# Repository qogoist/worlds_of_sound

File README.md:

# Worlds of Sound

* [Raspberry Pi/Column](/column_tof/pi_setup.md)
* [Arduino/Cube](/arduino_files/arduino_setup.md)

## Dev Tools
* [Max MSP](https://cycling74.com/products/max) is necessary to open the MAX patches which are used as plugins for Ableton.
* [Arduino IDE](https://www.arduino.cc/en/Main/Software) is needed to get the necessary drivers and libraries to write and upload code to the Arduinos.

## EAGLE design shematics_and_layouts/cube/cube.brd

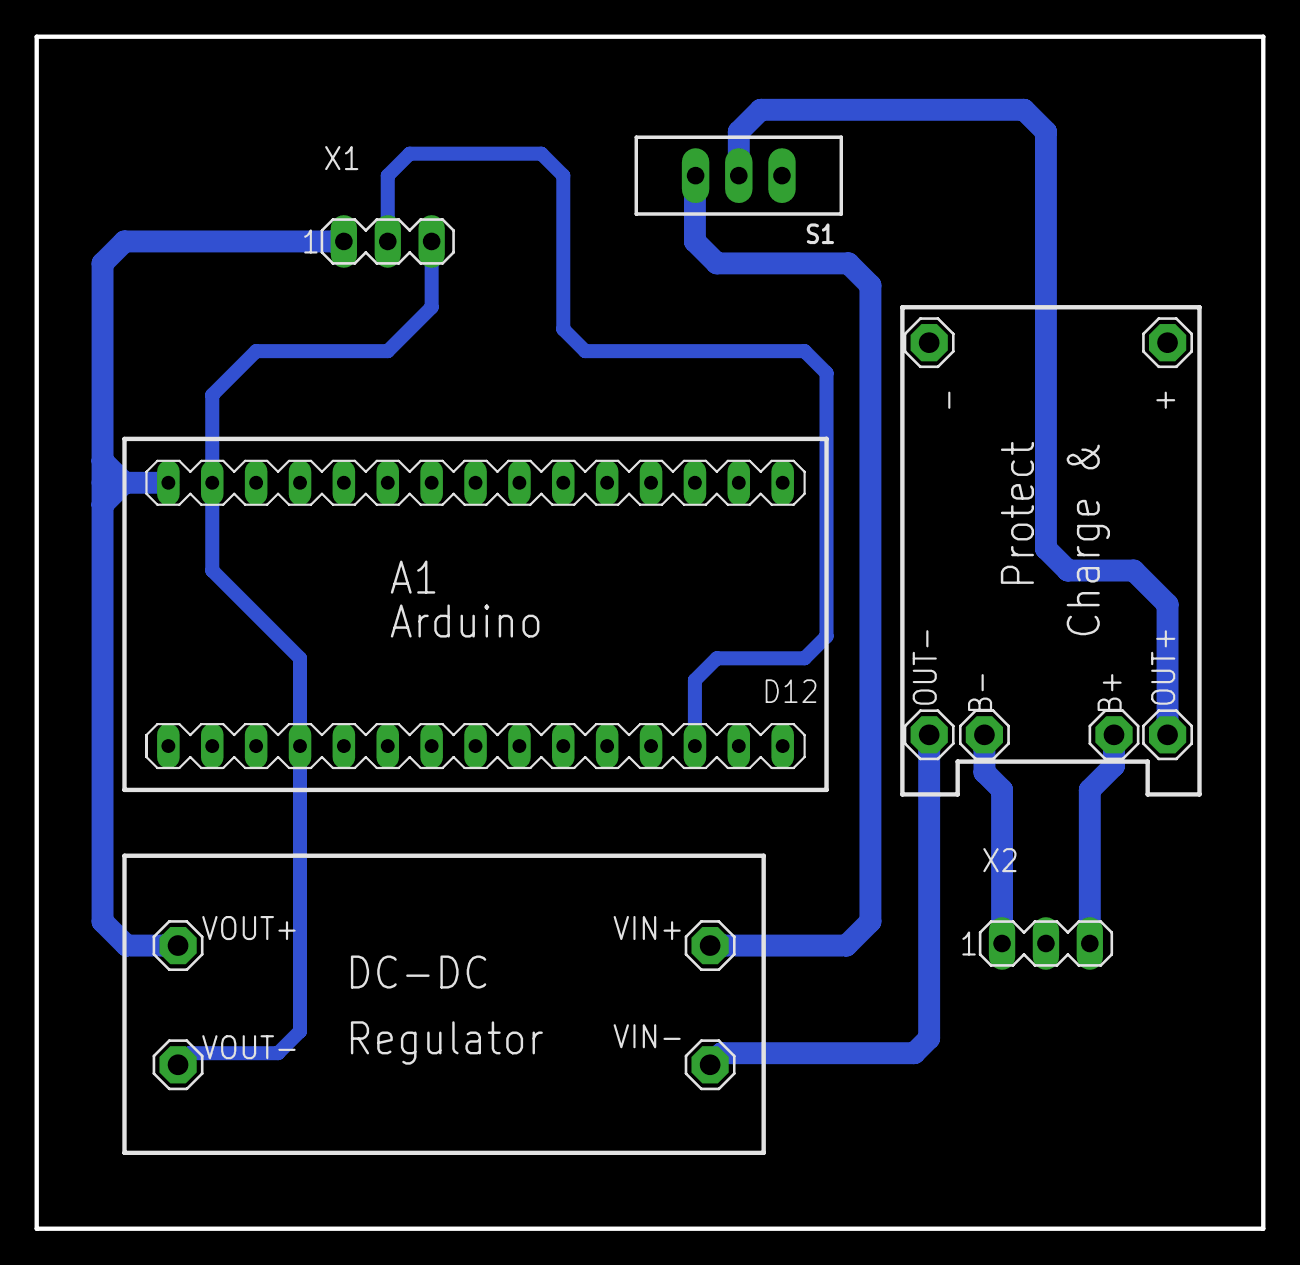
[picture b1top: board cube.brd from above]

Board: 2 copper layers, 71.0 x 69.0 mm, 14 parts (0 on the bottom side), 8 nets.

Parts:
+: MCS08
-: MCS08
A1: NANO
B+: MCS08
B-: MCS08
OUT+: MCS08
OUT-: MCS08
S1: EG1218
VIN+: MCS08
VIN-: MCS08
VOUT+: MCS08
VOUT-: MCS08
X1: LEDs; MA03-1
X2: BAT; MA03-1

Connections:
GND: A1.GND, A1.GND1, VOUT-.MP, X1.3
unnamed: OUT+.MP, S1.2
unnamed: OUT-.MP, VIN-.MP
unnamed: S1.3, VIN+.MP
unnamed: B-.MP, X2.1
unnamed: B+.MP, X2.3
unnamed: A1.D10, X1.2
VCC: A1.RAW, VOUT+.MP, X1.1

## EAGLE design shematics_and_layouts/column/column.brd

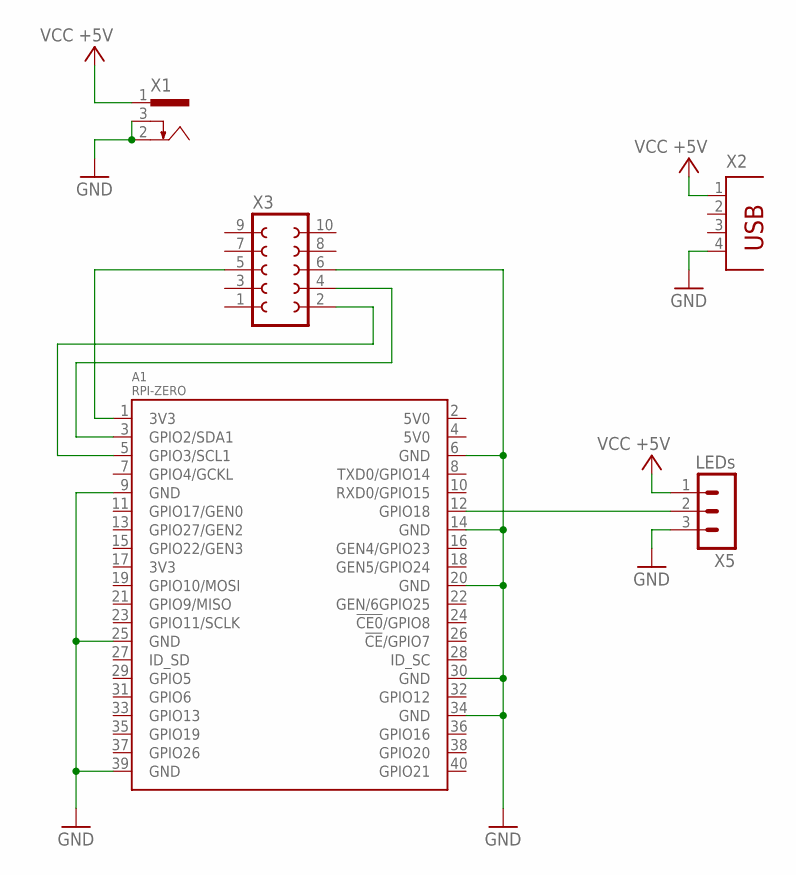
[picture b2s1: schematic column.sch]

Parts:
A1: RPI-ZERO; RASP_PI_ZERO_BOARD_FULL
X1: 733980-62
X2: PN87520
X3: FE05-2
X5: LEDs; MA03-1

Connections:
3V3@1: A1.1 (3V3), X3.5
GND: A1.6 (GND), A1.9 (GND), A1.14 (GND), A1.20 (GND), A1.25 (GND), A1.30 (GND), A1.34 (GND), A1.39 (GND), X1.2, X1.3, X2.4, X3.6, X5.3
unnamed: A1.5 (GPIO3/SCL1), X3.2
unnamed: A1.3 (GPIO2/SDA1), X3.4
unnamed: A1.12 (GPIO18), X5.2
VCC: X1.1, X2.1, X5.1

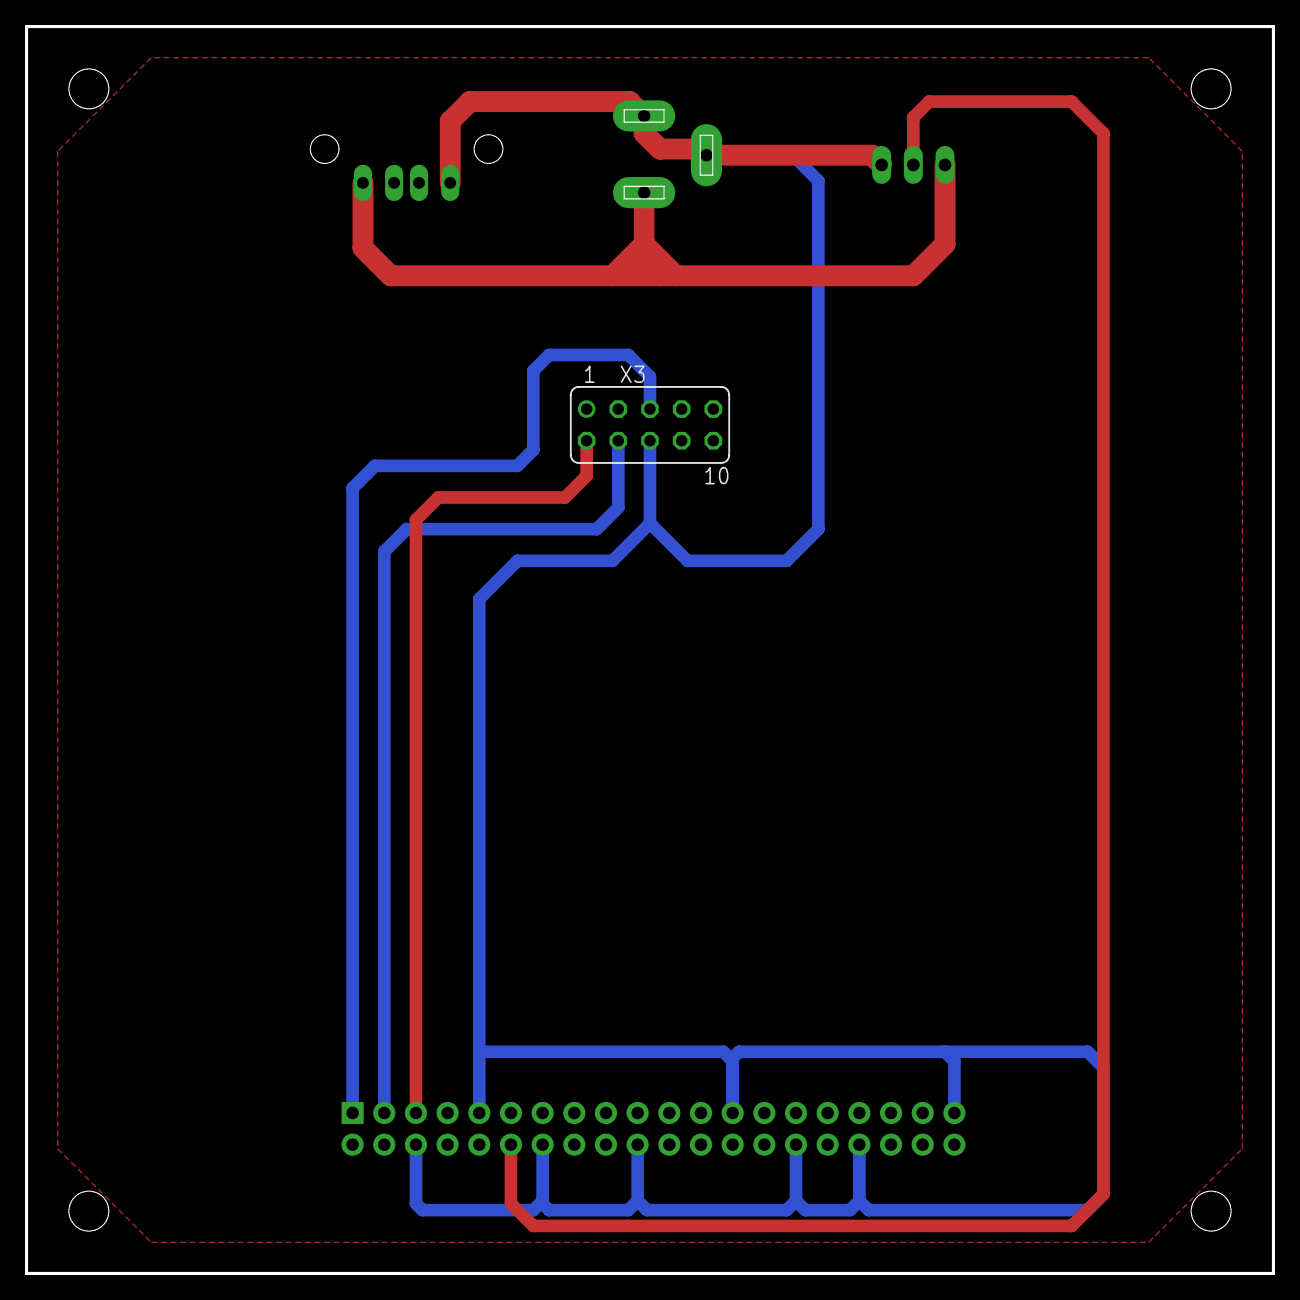
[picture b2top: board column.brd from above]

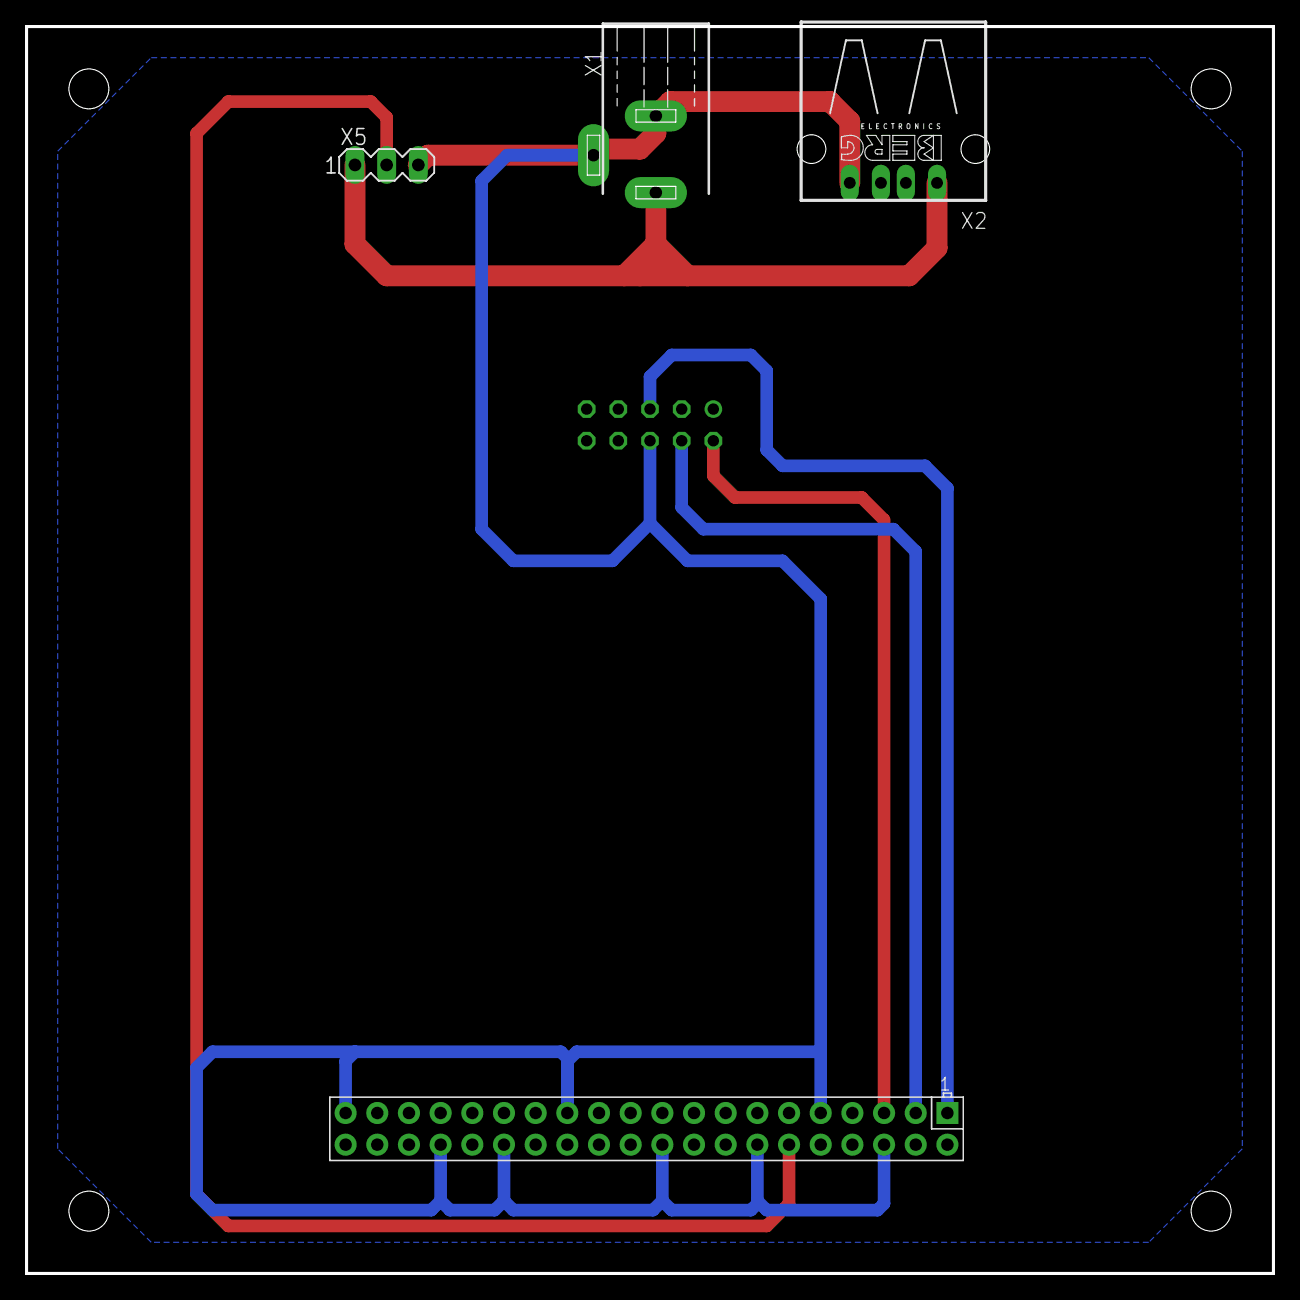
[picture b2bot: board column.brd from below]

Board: 2 copper layers, 100.0 x 100.0 mm, 5 parts (4 on the bottom side), 6 nets.

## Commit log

2019-11-01 initialize .gitignore
2019-11-01 add BASIC_MIDI_OUTPUT and README
2019-11-01 added LED strip functionality
2019-11-18 Added ultrasonic controller
2019-11-18 TASK: created a IR sensor sketch with denoising
2019-11-25 TASK: created a accelerometer folder & addet a poti routine to the ir_reciver
2019-11-25 TASK: Updated README
2019-11-25 TASK: accelerometer base scetch with comments and raw value serial output
2019-11-26 TASK: corrected typo
2019-11-28 TASK: addet editable thresholds for orientation detection & midi note output for accelerometer
2019-11-29 accelerometer velocity changes
2019-11-29 Changed midi notes and sites
    Doesn't continuously send notes, but just on trigger.
2019-11-29 Format cleanup in accelerometer
2019-11-30 added basic drumroll routine & changed names for existing controllers
    To match new naming scheme, should always be "[type of controller]_controller"
2019-12-03 Added delay to drum controller
2019-12-10 Updated drum controller to act as switches
2019-12-10 updated drum controller to actually work like a switch, lel
2019-12-10 removed unnecesary notes
    TOPKEK ECKSDEE
2019-12-17 Added cube_continuous_controller
2020-03-14 updated continuous to testing stage
2020-03-14 Added continuous cube
2020-03-14 changed folder structure
2020-03-14 Updated scaling for continuous controller
2020-03-14 colorDetection
2020-03-16 TASK: TOF Code and readme
2020-03-16 TASK: addet tof-pi wireing/winout image
2020-03-16 TASK: Raspberry Pi setup stuff
2020-03-16 TASK: addet script
2020-03-27 Updated continuous controller
    Now provides an additional OSC message giving the current side on top.
2020-03-27 Updated basic routing max patch
    Reflects the changes to updated continuous controller
2020-03-31 added Treshold for currentSide
2020-04-16 TASK: Addet empty shematic files for column and cube
2020-04-17 TASK: Basic and ugly cube shematic
2020-04-17 TASK: Updated Partlist
2020-04-24 TASK: cube shematic and board --> addet all componets, for now
2020-04-29 TASK: Correct Shematic to new Arduino IoT
2020-04-29 TASK: Board outlines for U-Suply components
2020-05-04 TASK: finished layout Cube
2020-05-13 TASK: Increased ranging speed, edited setup readme and addet a settings section at the top of the file
2020-05-13 Updated continuous controller
    Added LED control based on incoming OSC messages. Messages should follow the pattern "/sideX H S V".
    Now sends and receives OSC messages via UDP rather than Serial. Serial is currently still required to start the loop, due to debugging issues.
    Updated max patch to reflect the changes to the arduino.
    Cleaned up various files.
2020-05-20 Updated continuous controller
2020-05-20 MasterReciever & LocalReceiver
2020-05-20 Neues Sounddesign
    Sounds: Lead, Kick, Bass
2020-05-20 Ableton_removed
2020-05-20 slim max patcher
2020-05-20 column activated
2020-05-20 all patches
2020-06-02 TASK: setup IP adresses and ports
2020-06-03 TASK: Testing PiZero Lib
2020-06-04 TASK: Add switch to cube
2020-06-08 TASK: col shematic
2020-06-08 TASK: col brd, part placement
2020-06-10 TASK: Layout col, remove holes in pi
2020-06-14 TASK: generated gerber files for ordering
2020-06-18 Changed led_test to simple led testting routine
2020-06-18 Code Cleanup
2020-06-21 Master Receiver v2
2020-06-24 Change Raspi to broadcast to network
2020-06-24 Change led test for testing purposes
2020-06-24 Update Readme to reflect latest changes
2020-06-24 Update cube controller to latest version
2020-06-26 Remove Sleep Timer & Add Hash to make script executable
2020-07-02 TASK: setup Neopixel LEDS and edit README
2020-07-02 TASK: Addet OSC support for LED control, fixed rangeing bug and capet rangeing
2020-07-04 Bugfixing'n stuff Säulen
2020-07-04 Change to OSC adresses to make it easier to change
2020-07-08 Change behaviour of leds
    Pi now scales the brightness of LEDS without input through OSC
    Max/Min Brightness, Cutoff, LED Color can be set via OSC messages
2020-07-08 Updated Readmes
2020-08-08 deleting unnecessary files and updating readme
2020-08-08 readme updates
2020-08-09 TASK: fixed Comments

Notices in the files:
parts and their libraries:
switch-e-switch: Copyright (C) 2010, Bob Starr
